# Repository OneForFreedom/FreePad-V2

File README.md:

# FreePad-V2

This is FreePad V2, the latest of my creations!

It contains 15 switches and one rotary encoder! 

You may ask whats v1? well v1 was a 5x3 layout with 3 of the 15 switches being a rotary encoder. It used a raspberry pi pico. This one uses a Seeed Xiao Rp2040 which saves loads on space!

It is also VERY slimmed down then the hungus and chungus of the FreePad V1

I hope you love it!

## Who doesn't love a little visuals?

## BOM (Cuz otherwise how are you gonna make the damn thing?!)

| BOM Name     | Quantity |
| ------------ | -------- |
| switches     | 15       |
| diode        | 15       |
| XIAO-RP2040  | 1        |
| encoder      | 1        |
| keycap-white | 15       |

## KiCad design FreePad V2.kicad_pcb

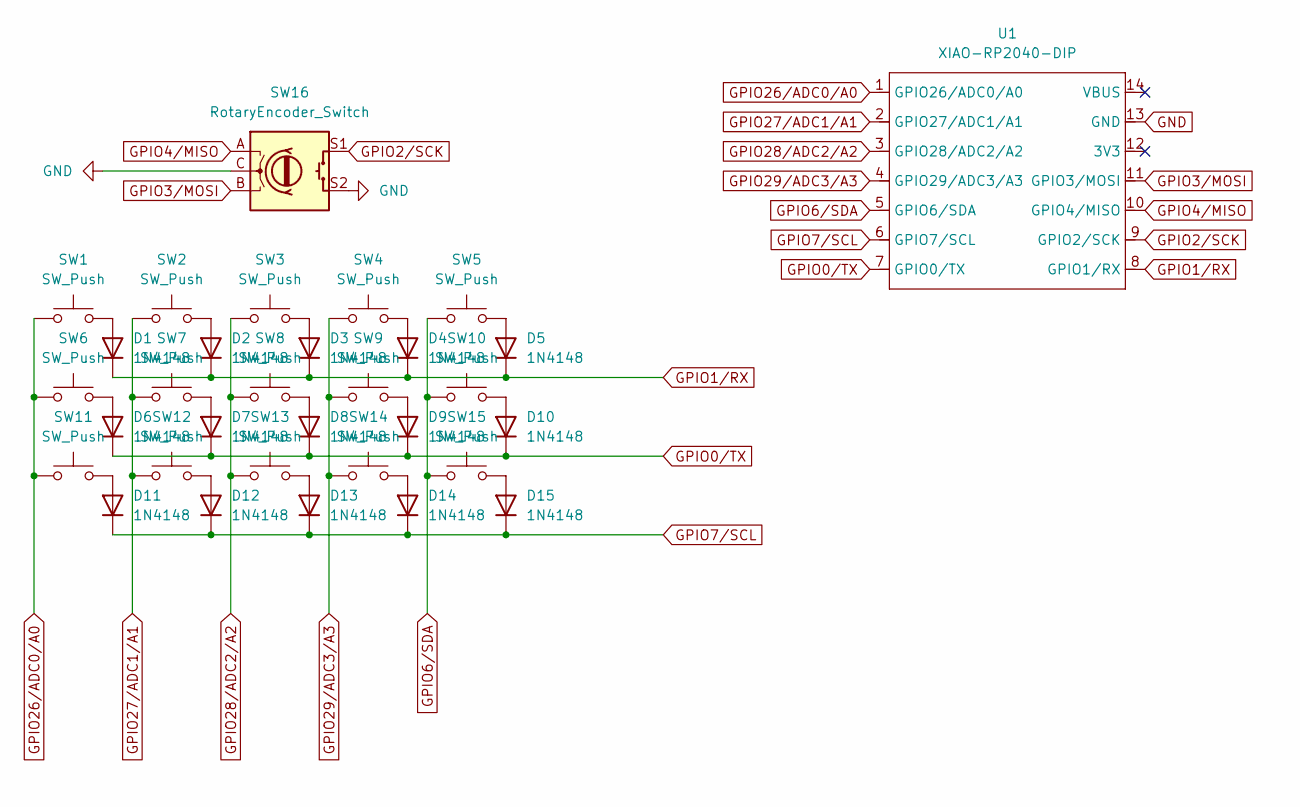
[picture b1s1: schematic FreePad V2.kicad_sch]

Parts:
D1, D2, D3, D4, D5, D6, D7, D8, D9, D10, D11, D12, D13, D14, D15: 1N4148; D_DO-35_SOD27_P7.62mm_Horizontal
SW1, SW2, SW3, SW4, SW5, SW6, SW7, SW8, SW9, SW10, SW11, SW12, SW13, SW14, SW15: SW_Push; SW_Cherry_MX_1.00u_PCB WITH 3D
SW16: RotaryEncoder_Switch; RotaryEncoder_Alps_EC11E-Switch_Vertical_H20mm
U1: XIAO-RP2040-DIP

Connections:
GND: SW16.C, SW16.S2, U1.13 (GND)
GPIO0/TX: D6.1 (K), D7.1 (K), D8.1 (K), D9.1 (K), D10.1 (K), U1.7 (GPIO0/TX)
GPIO1/RX: D1.1 (K), D2.1 (K), D3.1 (K), D4.1 (K), D5.1 (K), U1.8 (GPIO1/RX)
GPIO2/SCK: SW16.S1, U1.9 (GPIO2/SCK)
GPIO3/MOSI: SW16.B, U1.11 (GPIO3/MOSI)
GPIO4/MISO: SW16.A, U1.10 (GPIO4/MISO)
GPIO6/SDA: SW5.1, SW10.1, SW15.1, U1.5 (GPIO6/SDA)
GPIO7/SCL: D11.1 (K), D12.1 (K), D13.1 (K), D14.1 (K), D15.1 (K), U1.6 (GPIO7/SCL)
GPIO26/ADC0/A0: SW1.1, SW6.1, SW11.1, U1.1 (GPIO26/ADC0/A0)
GPIO27/ADC1/A1: SW2.1, SW7.1, SW12.1, U1.2 (GPIO27/ADC1/A1)
GPIO28/ADC2/A2: SW3.1, SW8.1, SW13.1, U1.3 (GPIO28/ADC2/A2)
GPIO29/ADC3/A3: SW4.1, SW9.1, SW14.1, U1.4 (GPIO29/ADC3/A3)
unnamed: D1.2 (A), SW1.2
unnamed: D2.2 (A), SW2.2
unnamed: D3.2 (A), SW3.2
unnamed: D4.2 (A), SW4.2
unnamed: D5.2 (A), SW5.2
unnamed: D6.2 (A), SW6.2
unnamed: D7.2 (A), SW7.2
unnamed: D8.2 (A), SW8.2
unnamed: D9.2 (A), SW9.2
unnamed: D10.2 (A), SW10.2
unnamed: D11.2 (A), SW11.2
unnamed: D12.2 (A), SW12.2
unnamed: D13.2 (A), SW13.2
unnamed: D14.2 (A), SW14.2
unnamed: D15.2 (A), SW15.2

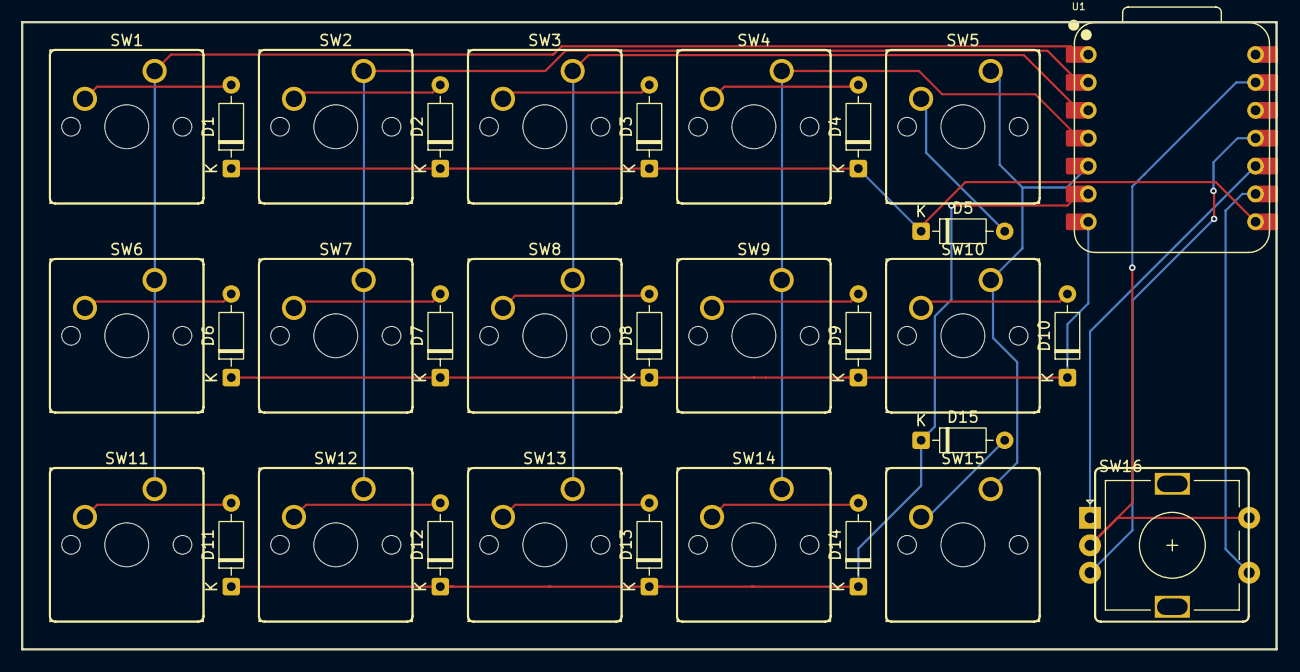
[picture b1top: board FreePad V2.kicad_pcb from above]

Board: 2 copper layers, 114.4 x 57.2 mm, 32 parts (0 on the bottom side), 27 nets.

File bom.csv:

Designator,Footprint,Quantity,Value,LCSC Part #
"D1, D10, D11, D12, D13, D14, D15, D2, D3, D4, D5, D6, D7, D8, D9",D_DO-35_SOD27_P7.62mm_Horizontal,15,1N4148,
"SW1, SW10, SW11, SW12, SW13, SW14, SW15, SW2, SW3, SW4, SW5, SW6, SW7, SW8, SW9",SW_Cherry_MX_1.00u_PCB WITH 3D,15,SW_Push,
SW16,RotaryEncoder_Alps_EC11E-Switch_Vertical_H20mm,1,RotaryEncoder_Switch,
U1,XIAO-RP2040-DIP,1,XIAO-RP2040-DIP,

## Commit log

2025-08-29 Rename FreePad_V2.zip to Production/FreePad_V2.zip
2025-08-29 Rename Screenshot 2025-08-29 215546.png to Images/Screenshot 2025-08-29 215546.png
